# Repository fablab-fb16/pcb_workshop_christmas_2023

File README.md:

# Blinky Christmas Tree Ball - Soldering Kit
This Readme is in English. For German, see [README DE.md](/README%20DE.md).

Designed by Stefan Kablowski, Max Lindemann, Janos Föth.

Soldering workshop kindly sponsored by VDE Bezirksverein Kassel e. V.

## Quick Links

- [Detailed Build Instructions (EN)](/documentation/Build%20Instructions.md) / [Detaillierte Bauanleitung (DE)](/documentation/Build%20Instructions%20DE.md)
- [Assembly List](/documentation/Assembly%20List.md)
- [Usage Instructions (EN)](/documentation/Usage%20Instructions.md) / [Gebrauchsanleitung (DE)](/documentation/Usage%20Instructions%20DE.md)
- [Schematics](/documentation/schematics.md)
- [Interactive BOM](https://fablab-fb16.github.io/pcb_workshop_christmas_2023/)

## Features
- Interactive: Adjustable blinking pattern and speed via two potentiometers
- Daisy-Chaining possible: Connect multiple christmas balls and push signals from master down the line for various patterns

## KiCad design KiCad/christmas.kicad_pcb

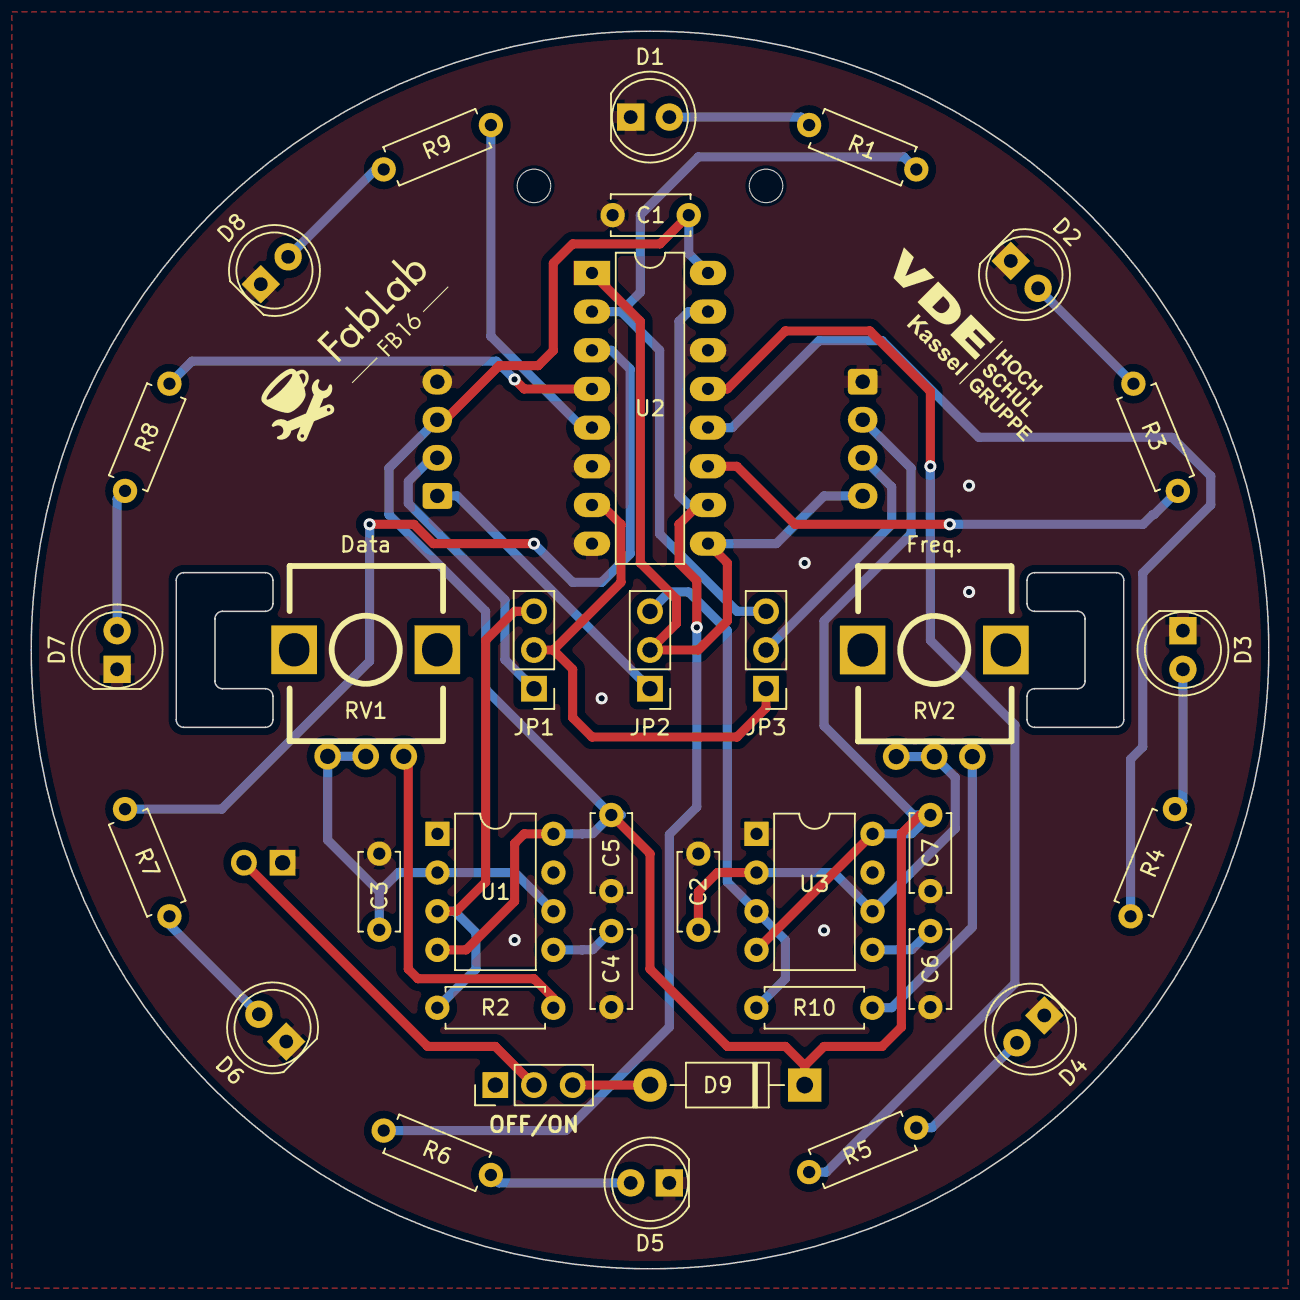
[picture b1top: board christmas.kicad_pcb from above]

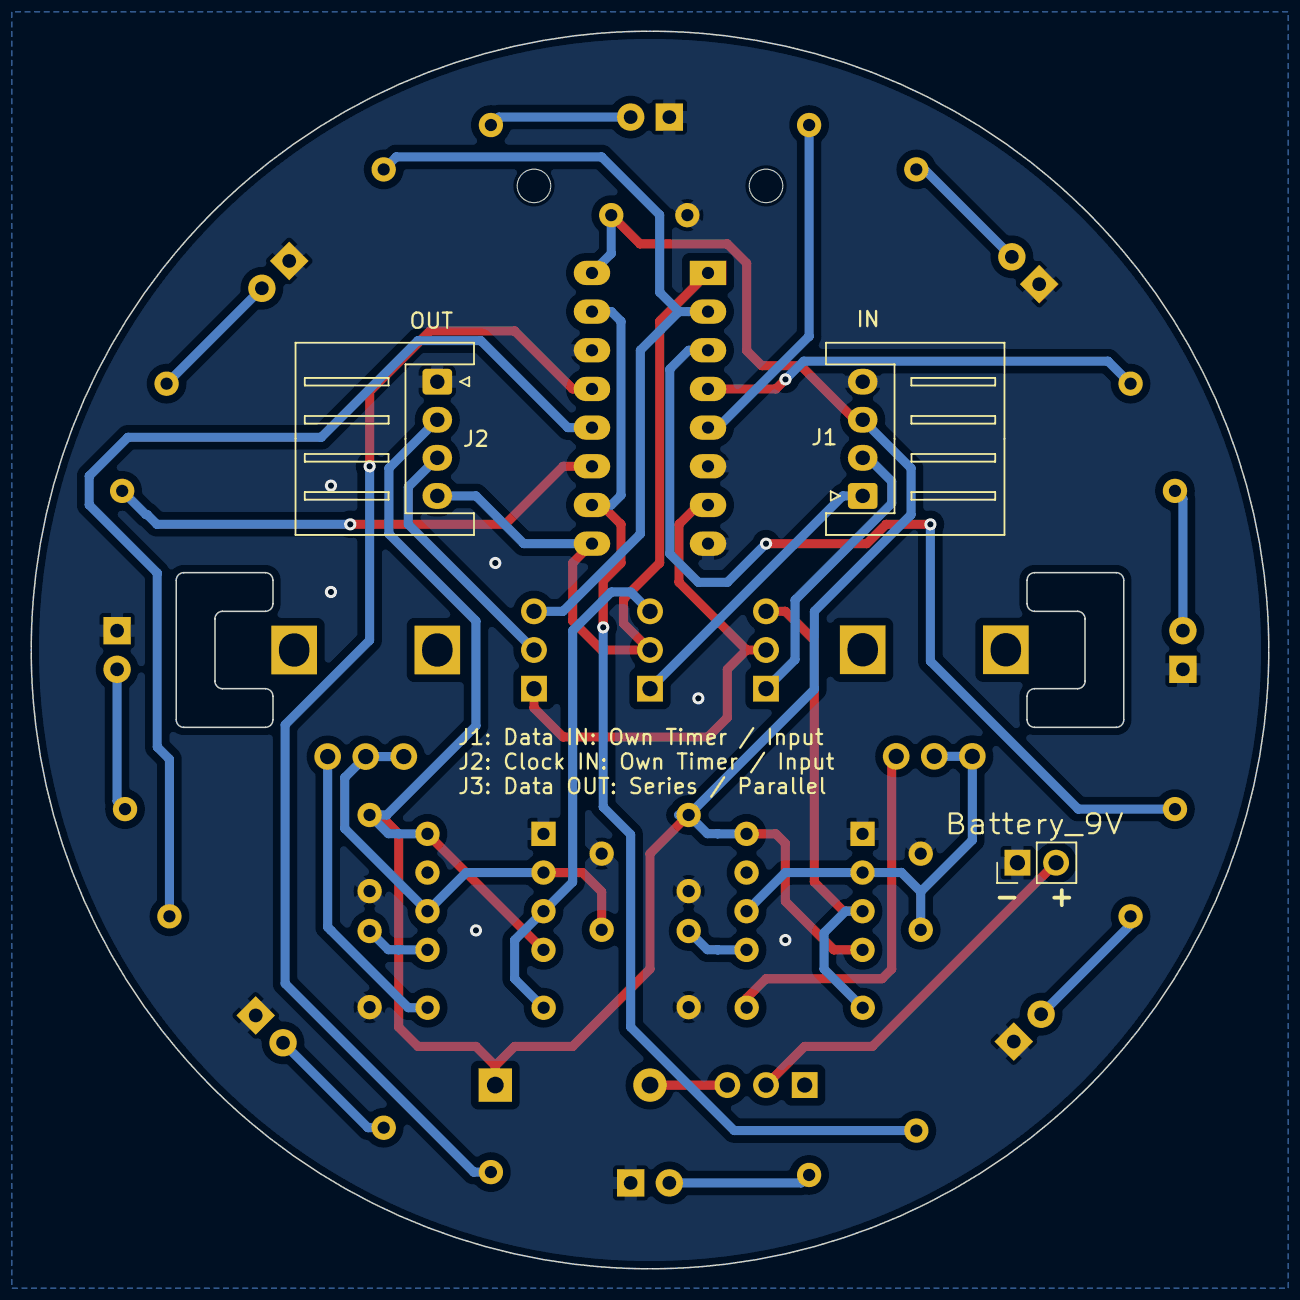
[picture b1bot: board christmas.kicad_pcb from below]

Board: 2 copper layers, 81.3 x 81.3 mm, 40 parts (3 on the bottom side), 33 nets.

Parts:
C1, C4, C5, C6, C7: 100n; C_Disc_D5.0mm_W2.5mm_P5.00mm
C2, C3: 4.7u; C_Disc_D5.0mm_W2.5mm_P5.00mm
D1, D2, D3, D4, D5, D6, D7, D8: LED; LED_D5.0mm
D9: 1N5817; D_DO-41_SOD81_P10.16mm_Horizontal
H1, H2: MountingHole; MountingHole_2.2mm_M2
J1, J2: Conn_01x04; JST_XH_S4B-XH-A_1x04_P2.50mm_Horizontal
J3: Battery_9V; PinHeader_1x02_P2.54mm_Vertical
JP1, JP2, JP3: Jumper_3_Open; PinHeader_1x03_P2.54mm_Vertical
ON/OFF1: Jumper_3_Open; PinHeader_1x03_P2.54mm_Vertical
R1, R3, R4, R5, R6, R7, R8, R9: 1.4k; R_Axial_DIN0207_L6.3mm_D2.5mm_P7.62mm_Horizontal
R2, R10: 10k; R_Axial_DIN0207_L6.3mm_D2.5mm_P7.62mm_Horizontal
RV1, RV2: 1M; RV09AF-40-ALPHA-POT
U1, U3: NE555P; DIP-8_W7.62mm
U2: 4015; DIP-16_W7.62mm_LongPads

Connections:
/Clk: J1.1, JP2.1 (A)
/Data: J1.2, JP1.1 (A)
/Timer1/Out: JP2.3 (B), R10.2, U3.3 (Q)
/Timer/Out: JP1.3 (B), R2.2, U1.3 (Q)
GND: C1.1, C2.1, C3.1, C4.1, C5.1, C6.1, C7.1, D1.1 (K), D2.1 (K), D3.1 (K), D4.1 (K), D5.1 (K), D6.1 (K), D7.1 (K), D8.1 (K), J1.4, J2.1, J3.1, U1.1 (GND), U2.6 (MR), U2.8 (Vss), U2.14 (MR), U3.1 (GND)
unnamed: D1.2 (A), R1.2
unnamed: D2.2 (A), R3.2
unnamed: D3.2 (A), R4.2
unnamed: D4.2 (A), R5.2
unnamed: D5.2 (A), R6.2
unnamed: D6.2 (A), R7.2
unnamed: D7.2 (A), R8.2
unnamed: D8.2 (A), R9.2
unnamed: D9.2 (A), ON/OFF1.3 (B)
unnamed: J2.3, JP3.2 (C)
unnamed: J2.4, JP2.2 (C), U2.1 (CP), U2.9 (CP)
unnamed: J3.2, ON/OFF1.2 (C)
unnamed: JP1.2 (C), JP3.1 (A), U2.7 (D)
unnamed: JP3.3 (B), R1.1, U2.2 (Q4)
unnamed: R2.1, RV1.3
unnamed: R10.1, RV2.3
unnamed: C4.2, U1.5 (CV)
unnamed: C3.2, RV1.1, RV1.2, U1.2 (TR), U1.6 (THR)
unnamed: R9.1, U2.5 (Q1)
unnamed: R8.1, U2.4 (Q2)
unnamed: R7.1, U2.3 (Q3)
unnamed: R6.1, U2.10 (Q4), U2.15 (D)
unnamed: R5.1, U2.13 (Q1)
unnamed: R4.1, U2.12 (Q2)
unnamed: R3.1, U2.11 (Q3)
unnamed: C6.2, U3.5 (CV)
unnamed: C2.2, RV2.1, RV2.2, U3.2 (TR), U3.6 (THR)
VCC: C1.2, C5.2, C7.2, D9.1 (K), J1.3, J2.2, U1.4 (R), U1.8 (VCC), U2.16 (Vdd), U3.4 (R), U3.8 (VCC)

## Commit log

2023-11-11 Add KiCad Sketch
2023-11-11 minor fixes
2023-11-12 added pictures
2023-11-12 added notebook and more pictures
2023-11-12 minor fixchanges
2023-11-13 major fixes
2023-11-13 generated and zipper JLC-PCB gerber files
2023-11-17 add fablab and vde logos, add rubber band battery holder cutouts
2023-11-17 rewire board2board connector to match "same direction" cables
2023-11-29 Add to do for final pcb
2023-11-30 restructure components on board and implement ToDos from prototyping
2023-12-01 update Shiftregister package
2023-12-01 Added frequency label on front silkscreen for poti
2023-12-01 Moved Frequency Label
2023-12-01 switch Poti wiring, adjust to JLCPCB design rules
2023-12-05 generate Gerber; FINAL ORDER VERSION
2023-12-05 add drc exclusions
2023-12-12 update interactive BOM
2023-12-13 add documentation (first version, without images)
2023-12-13 Update Build Instructions.md
    fix coloring and wrong content
2023-12-14 add images to instructions
2023-12-14 resize images
2023-12-14 Rename 050_shift_register_detail.JPG to 050_shift_register_detail.jpg
2023-12-14 Rename 051_shift_register_done.JPG to 051_shift_register_done.jpg
2023-12-14 Rename ibom.html to index.html
2023-12-14 Rename bom.yml to ibom.yml
2023-12-14 Update README.md: add interactive BOM link
2023-12-14 add german build instructions
2023-12-14 Update Build Instructions DE.md: fix typos
2023-12-14 This commit will be automatically published
2023-12-14 Automated publish
2024-01-07 Update Usage Instructions.md: add more detailed information
2024-01-07 Add german translation for Usage Instructions
2024-01-07 Update README.md: add link to german Usage Instructions
2024-01-07 Add german translation for README.md
2024-01-07 Update README.md and README DE.md: update language hints for links
2024-01-07 Update README DE.md: fix spelling
